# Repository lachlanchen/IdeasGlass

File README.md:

[English](README.md) · [العربية](i18n/README.ar.md) · [Español](i18n/README.es.md) · [Français](i18n/README.fr.md) · [日本語](i18n/README.ja.md) · [한국어](i18n/README.ko.md) · [Tiếng Việt](i18n/README.vi.md) · [中文 (简体)](i18n/README.zh-Hans.md) · [中文（繁體）](i18n/README.zh-Hant.md) · [Deutsch](i18n/README.de.md) · [Русский](i18n/README.ru.md)

# IdeasGlass

*A wearable AI glass that turns ideas into actions, income, and creative momentum.*

> Voice-first wearable AI pipeline: capture from ESP32 glasses, process in FastAPI, and monitor/control via a live PWA dashboard.

| Lane | Purpose |
|---|---|
| 🎙️ Wearable capture | ESP32 glasses send audio, photos, and telemetry in near-real-time |
| 🧠 Backend intelligence | FastAPI ingests streams, transcribes, segments, and persists metadata |
| 🖥️ Dashboard | PWA shows live waveform, transcripts, and device/account status |

<div align="center">

  <br/>
  <sub>App UI (left) · Hardware (right)</sub>
</div>

Explore community experiments at <a href="https://onlyideas.art">onlyideas.art</a>.

## 🚀 Overview

IdeasGlass is an AI-first wearable system for voice-first idea capture and execution. In this repository, the primary runtime path is:

- `backend/glass/` for FastAPI APIs, WebSocket ingest, Whisper-based transcription, and the installable PWA dashboard.
- `IdeaGlass/firmware/ideasglass_arduino/IdeasGlassClient/` for XIAO ESP32S3 firmware streaming telemetry/audio/photos.

If you are new to this repo, start there first.

## 📚 Table of Contents

- [🚀 Overview](#-overview)
- [✨ Why IdeasGlass](#-why-ideasglass)
- [🧩 Features](#-features)
- [🔄 Sample Workflow](#-sample-workflow)
- [🗂️ Project Structure](#-project-structure)
- [🧰 Prerequisites](#-prerequisites)
- [⚙️ Installation](#️-installation)
- [▶️ Usage](#️-usage)
- [🛠️ Configuration](#️-configuration)
- [🧪 Examples](#-examples)
- [🧭 Development Notes](#-development-notes)
- [🆘 Troubleshooting](#️-troubleshooting)
- [🌐 Ecosystem Links](#-ecosystem-links)
- [🙏 Acknowledgements](#-acknowledgements)
- [🛣️ Roadmap](#️-roadmap)
- [🤝 Contribution](#-contribution)
- [❤️ Support](#-support)
- [📄 License](#-license)

### At a glance

| Area | Primary location | What it does |
|---|---|---|
| Backend API + PWA | `backend/glass/` | FastAPI endpoints, WebSocket ingest/fanout, transcription, dashboard |
| Firmware | `IdeaGlass/firmware/ideasglass_arduino/IdeasGlassClient/` | ESP32 capture/streaming client |
| Bridge notes | `references/ideasglass_bridge.md` | TLS/WAN reliability notes and deployment field tips |
| README translations | `i18n/` | Multilingual docs synced from the canonical README |

## ✨ Why IdeasGlass

IdeasGlass is an AI-first wearable built for people who live in streams of ideas. It captures, translates, organizes, and executes on creativity the moment inspiration strikes, whether you are narrating a concept in motion or hosting a live session.

## 🧩 Features

### Product vision features

- **Creation-native hardware** – lightweight glasses and wearable inputs, tuned for voice-first capture plus subtle gesture shortcuts.
- **Instant translation** – real-time language detection/translation so you can ideate across teams or audiences without switching tools.
- **EchoMind co-pilot** – tight pairing with `chat.lazying.art` for brainstorming, script drafting, and multilingual content coaching.
- **Channel autopilot** – drafts outlines, long-form scripts, short-form hooks, and schedules uploads to YouTube or other feeds.
- **Highlights & reels** – auto-selects moments, generates thumbnails, subtitles, and social-ready clips.
- **Income layer** – connects to LazyingArt Coin for tipping, credit payouts, and conversion to on-chain assets.
- **Spending & focus** – tracks operational spend, surfaces profitable formats, and distills your personal strengths into next projects.

### Repository/runtime features

- FastAPI backend with REST + WebSocket endpoints for ingest (`/api/v1/audio`, `/ws/audio-ingest`) and live stream fanout (`/ws/stream`).
- Deterministic audio segmentation (default ~15 s with overlap) into `backend/glass/audio_segments/`.
- Optional openai-whisper streaming transcripts with configurable latency thresholds.
- Optional Postgres persistence (`DATABASE_URL`) for messages, photos, chunks, segments, transcripts.
- PWA dashboard with live waveform, transcript updates, and install support on desktop/mobile.
- Arduino firmware support for XIAO ESP32S3 Sense camera + mic flows.

## 🔄 Sample Workflow

1. **Capture** – Speak or sketch a concept; IdeasGlass transcribes, translates, and tags the intent.
2. **Co-create** – EchoMind refines the idea, drafts scripts, and suggests CTAs tailored for each platform.
3. **Publish** – The channel agent auto-produces highlight videos, gallery images, and uploads them with metadata.
4. **Monetize** – Credits route through LazyingArt Coin (`coin.lazying.art`) and payouts sync with your preferred wallets.
5. **Reflect** – Spending, reach, and engagement dashboards surface what to double down on next.

## 🗂️ Project Structure

```text
IdeasGlass/
├── README.md
├── i18n/                                  # README translations
├── backend/
│   ├── glass/                             # Primary FastAPI + PWA backend
│   │   ├── app.py
│   │   ├── serve.py
│   │   ├── requirements.txt
│   │   ├── static/
│   │   ├── tools/
│   │   └── audio_segments/
│   ├── tornado_app/                       # Secondary/parallel ingest backend path
│   ├── memo/
│   ├── memo_legacy/
│   └── ngrok_bridge/
├── IdeaGlass/firmware/ideasglass_arduino/
│   ├── IdeasGlassClient/
│   ├── config.h
│   ├── WifiTest/WifiTest.ino
│   ├── wifi_credentials.example.h
│   └── README.md
├── references/ideasglass_bridge.md        # Bridge + deployment notes
├── docs/                                  # Additional site/docs assets
├── development_plan/
├── app/
├── ops/observability/
├── ios-app-example/
├── figs/
├── seeed_studio_xiao_esp32s3_dev/
└── .auto-readme-work/
```

## 🧰 Prerequisites

- Python 3.10+
- `pip` (or conda environment with compatible Python)
- Optional: NVIDIA GPU + CUDA/cuDNN for faster Whisper inference
- Optional: PostgreSQL for persistence
- For firmware: Arduino IDE or `arduino-cli`, Seeed XIAO ESP32S3 Sense, PSRAM enabled

| Component | Requirement | Notes |
|---|---|---|
| Backend runtime | Python 3.10+, `pip` | Use venv or conda (`glass`) |
| GPU acceleration (optional) | NVIDIA + CUDA/cuDNN | Improves Whisper latency |
| Persistence (optional) | PostgreSQL | Enabled via `DATABASE_URL` |
| Firmware toolchain | Arduino IDE / `arduino-cli` | Use XIAO ESP32S3 profile with PSRAM |

## ⚙️ Installation

### Backend dependencies

```bash
cd backend/glass
python -m venv .venv
source .venv/bin/activate
pip install -r requirements.txt
```

### Firmware prerequisites

- Copy `IdeaGlass/firmware/ideasglass_arduino/wifi_credentials.example.h` to `wifi_credentials.h` (recommended) and set SSID/password.
- In Arduino IDE, use board `ESP32 -> XIAO_ESP32S3` with `PSRAM: OPI PSRAM`.
- Partition scheme: `Default with spiffs (3MB APP/1.5MB SPIFFS)` or `Maximum APP` when filesystem is not needed.

## ▶️ Usage

### Run backend (uvicorn)

```bash
IDEASGLASS_WHISPER_MODEL=base IDEASGLASS_WHISPER_DEVICE=cuda \
uvicorn backend.glass.app:app \
  --host 0.0.0.0 \
  --port 8765 \
  --proxy-headers \
  --forwarded-allow-ips="*" \
  --reload
```

### Run backend (helper)

```bash
python backend/glass/serve.py --whisper-model base --whisper-device cuda --reload
```

### Open dashboard

- `http://localhost:8765/`
- `http://localhost:8765/healthz`

| Endpoint | Purpose |
|---|---|
| `/` | Main dashboard (PWA-capable UI) |
| `/healthz` | Backend liveness check |
| `/ws/audio-ingest` | Device ingest WebSocket |
| `/ws/stream` | Live stream fanout to dashboard clients |

### Login and bind your device

1. Register or login from the dashboard Settings/Account area.
2. Bind your device ID in the `Bind device` field.
3. Only bound devices will stream to your account.

Generate a device ID + QR image:

```bash
python backend/glass/tools/generate_device_id.py --out logs/device-id.png
```

Bind through API (cookie session required):

```bash
curl -X POST http://localhost:8765/api/v1/devices/bind \
  -H 'Content-Type: application/json' \
  -d '{"device_id":"<your-device-id>"}' \
  -b cookies.txt -c cookies.txt
```

Verify current account and bound devices:

```bash
curl -s http://localhost:8765/api/v1/auth/me -b cookies.txt -c cookies.txt | jq
```

Optional migration (rename historical data to a new device ID):

```bash
curl -X POST http://localhost:8765/api/v1/devices/rename \
  -H 'Content-Type: application/json' \
  -d '{"from_id":"old-id","to_id":"<your-device-id>"}' \
  -b cookies.txt -c cookies.txt
```

### Firmware build/upload (Arduino CLI)

```bash
FQBN='esp32:esp32:XIAO_ESP32S3:PartitionScheme=default_8MB,PSRAM=opi'
SKETCH='IdeaGlass/firmware/ideasglass_arduino/IdeasGlassClient'
PORT='/dev/ttyACM0'

bin/arduino-cli compile --fqbn "$FQBN" "$SKETCH"
bin/arduino-cli upload -p "$PORT" --fqbn "$FQBN" "$SKETCH"
```

If port is busy: `fuser -k /dev/ttyACM0`.
If permission denied: `sudo usermod -aG dialout $USER` then re-login (or temporary `sudo chmod a+rw /dev/ttyACM0`).

### Firmware power UX (XIAO ESP32S3)

- Hold the button ~0.8 s at power-up to boot.
- Hold ~2.5 s while running to enter deep sleep.
- Short press while running still triggers capture.

## 🛠️ Configuration

### Core environment variables

- `DATABASE_URL`: optional Postgres DSN for persistent storage.
- `IDEASGLASS_WHISPER_MODEL`: `base` (default), `small`, `medium`, `large-v3`, `large-v3-turbo`.
- `IDEASGLASS_WHISPER_DEVICE`: `cuda` or `cpu`.
- `IDEASGLASS_WHISPER_FP16`: `1` for GPU mixed precision, `0` for CPU.
- `IDEASGLASS_TRANSCRIBE`: `1` (default) to enable transcription, `0` to disable.
- `IDEASGLASS_TRANSCRIPT_INTERVAL_MS`: rolling transcript interval.
- `IDEASGLASS_TRANSCRIPT_THRESHOLDS_MS`: comma-separated thresholds (default `3000,6000,15000`).

| Variable | Default / options | Effect |
|---|---|---|
| `DATABASE_URL` | unset by default | Enables Postgres persistence for account/device data |
| `IDEASGLASS_WHISPER_MODEL` | `base` (`small`, `medium`, `large-v3`, `large-v3-turbo`) | Controls accuracy vs latency |
| `IDEASGLASS_WHISPER_DEVICE` | `cuda` or `cpu` | Inference backend |
| `IDEASGLASS_WHISPER_FP16` | `1` GPU, `0` CPU-safe | Mixed precision control |
| `IDEASGLASS_TRANSCRIBE` | `1` | Toggle transcription pipeline |
| `IDEASGLASS_TRANSCRIPT_INTERVAL_MS` | runtime configured | Rolling transcript push interval |
| `IDEASGLASS_TRANSCRIPT_THRESHOLDS_MS` | `3000,6000,15000` | Progressive transcript emission thresholds |

Safe `DATABASE_URL` examples:

- `export DATABASE_URL="postgresql://<db_user>@localhost/ideasglass_db"` (peer/local auth)
- `export DATABASE_URL="postgresql://<db_user>:<db_password>@localhost/ideasglass_db"` (password auth)

### Audio gain and segmentation knobs

- `IDEASGLASS_GAIN_TARGET` (default `0.032`)
- `IDEASGLASS_GAIN_MAX` (default `1.8`)
- `IDEASGLASS_GAIN_MIN_RMS` (default `0.008`)
- `IDEASGLASS_SPEECH_RMS` (default `0.03`)
- `IDEASGLASS_SPEECH_MARGIN` (default `0.005`)
- `IDEASGLASS_SEGMENT_TARGET_MS` (default `15000`)
- `IDEASGLASS_SEGMENT_OVERLAP_MS` (default `2000`)
- `IDEASGLASS_SEGMENT_GAIN_TARGET` (defaults to chunk gain target)

| Audio knob | Default | Purpose |
|---|---|---|
| `IDEASGLASS_GAIN_TARGET` | `0.032` | Target RMS normalization |
| `IDEASGLASS_GAIN_MAX` | `1.8` | Upper clamp for gain amplification |
| `IDEASGLASS_GAIN_MIN_RMS` | `0.008` | Floor to avoid amplifying near-silence |
| `IDEASGLASS_SPEECH_RMS` | `0.03` | Speech activity RMS baseline |
| `IDEASGLASS_SPEECH_MARGIN` | `0.005` | Margin around speech threshold |
| `IDEASGLASS_SEGMENT_TARGET_MS` | `15000` | Segment length target |
| `IDEASGLASS_SEGMENT_OVERLAP_MS` | `2000` | Segment overlap for continuity |
| `IDEASGLASS_SEGMENT_GAIN_TARGET` | inherits chunk gain | Segment-level normalization target |

### Model prefetch (optional)

```bash
python backend/glass/tools/prefetch_whisper_models.py \
  --models tiny,base,small,medium,large-v3 \
  --device cuda \
  --fp16 1
```

## 🧪 Examples

### Generate and bind a device ID

```bash
python backend/glass/tools/generate_device_id.py --out logs/device-id.png
```

Then set `kDeviceId` in:

- `IdeaGlass/firmware/ideasglass_arduino/IdeasGlassClient/IdeasGlassClient.ino`

Dashboard flow:

1. Register/login in Settings.
2. Bind the device in the Account panel.
3. Only bound devices stream to your account.

### REST ingest examples

```bash
curl -X POST http://localhost:8765/api/v1/messages \
  -H 'Content-Type: application/json' \
  -d '{"device_id":"dev-001","message":"hello from curl"}'
```

```bash
curl -X POST http://localhost:8765/api/v1/messages \
  -H 'Content-Type: application/json' \
  -d '{
    "device_id":"dev-001",
    "message":"photo demo",
    "photo_base64":"'"$(base64 -w0 sample.jpg)'"',
    "photo_mime":"image/jpeg"
  }'
```

```bash
rec --bits 16 --channels 1 --rate 16000 -c 1 -b 16 -e signed-integer temp.raw trim 0 0.25
curl -X POST http://localhost:8765/api/v1/audio \
  -H 'Content-Type: application/json' \
  -d '{
    "device_id":"dev-001",
    "sample_rate":16000,
    "bits_per_sample":16,
    "duration_ms":250,
    "rms":0.05,
    "audio_base64":"'"$(base64 -w0 temp.raw)'"'
  }'
```

```bash
curl http://localhost:8765/api/v1/audio/segments | jq '.[0]'
curl -o latest.wav http://localhost:8765/api/v1/audio/segments/<segment-id>
```

## 🧭 Development Notes

### Focus area

This repo contains multiple backend tracks. Current contributor guidance and runtime focus is `backend/glass/` unless otherwise requested.

### Static/syntax check

```bash
python -m compileall backend/glass/app.py
```

### Developer docs

- [IdeasGlass Object Analysis](OmiGlass/docs/ideasglass_analysis.mdx)
- [Arduino Hardware Blueprint](OmiGlass/docs/ideasglass_arduino_hardware.md)
- [Multi-platform App / PWA Plan](OmiGlass/docs/ideasglass_pwa_plan.md)
- [Bridge & Arduino HTTPS Client](docs/ideasglass_bridge.md)

> Note: In the current repository snapshot, some historical links above appear to have moved (for example, bridge notes now exist at `references/ideasglass_bridge.md`). The original links are preserved as canonical README content.

### Quick device binding (preserved workflow)

- Generate ID (in conda `glass`): `python backend/glass/tools/generate_device_id.py`
- Set it in firmware: `IdeaGlass/firmware/ideasglass_arduino/IdeasGlassClient/IdeasGlassClient.ino` (`kDeviceId`)
- Run backend and open `http://localhost:8765`, register/login, then bind the device ID in the Account panel

## 🆘 Troubleshooting

- **Port already in use:** run backend on another port and update client settings.
- **Serial port busy:** `fuser -k /dev/ttyACM0`.
- **Linux serial permission denied:** `sudo usermod -aG dialout $USER` and re-login.
- **Postgres unavailable:** backend can run without DB for partial functionality; verify `DATABASE_URL` and restart.
- **Whisper performance issues:** use smaller models (`base`/`small`) or disable transcription via `IDEASGLASS_TRANSCRIBE=0`.
- **TLS/time sync instability on ESP32:** verify Wi-Fi, NTP availability (UDP/123), and cert/host settings; see `references/ideasglass_bridge.md` for detailed field notes.
- **No live waveform updates:** check backend logs and browser console for `[IdeasGlass][wave]` traces and confirm `/ws/stream` connectivity.

## 🌐 Ecosystem Links

| Brand | Purpose | Link |
|---|---|---|
| 🧠 EchoMind | Multilingual AI companion for learning and creation | [chat.lazying.art](https://chat.lazying.art) |
| 🌱 OnlyIdeas | Research-to-product community for bold concepts | [onlyideas.art](https://onlyideas.art) |
| 💸 LazyEarn | Automations to turn small wins into income | [earn.lazying.art](https://earn.lazying.art) |
| 📚 LazyLearn | Physics & chemistry tracks and notebooks | [learn.lazying.art](https://learn.lazying.art) |
| 🤖 IdeasRobot | Agent that turns ideas into drafts, tasks, and posts | [robot.lazying.art](https://robot.lazying.art) |
| 👓 IdeasGlass | Capture, translate, and auto-produce highlight reels | [glass.lazying.art](https://glass.lazying.art) |
| 🪙 LazyingArt Coin | Rewards and payouts bridging contributions and on-chain value | [coin.lazying.art](https://coin.lazying.art) |
| 🧪 IDEAS | Notebook of research notes and essays | [ideas.onlyideas.art](https://ideas.onlyideas.art) |
| 🎨 LazyingArt | Studio behind OnlyIdeas, EchoMind, LazyEdit, and IdeasGlass | [lazying.art](https://lazying.art) |

## 🙏 Acknowledgements

We stand on the shoulders of great open projects — thank you to:

- <a href="https://www.omi.me/?ref=LazyingArt" target="_blank" rel="noopener" style="display:inline-flex;align-items:center;justify-content:center;padding:0.45rem 1rem;border-radius:999px;background:#111827;color:#ffffff;font-weight:700;text-decoration:none;">Get OmiGlass (BasedHardware)</a>
  - **Referral Program** — Use coupon `LazyingArt` to save 10% (30% commission unlocks after 10 sales).

    <div style="display:flex;flex-wrap:wrap;gap:0.4rem;margin:0.3rem 0;">
      <a href="https://www.omi.me/?ref=LazyingArt" target="_blank" rel="noopener" style="display:inline-flex;align-items:center;justify-content:center;padding:0.45rem 1.1rem;border-radius:999px;background:#111827;color:#ffffff;font-weight:700;text-decoration:none;">Get OmiGlass with LazyingArt</a>
      <a href="https://discord.com/invite/8MP3b9ymvx?ref=LazyingArt" target="_blank" rel="noopener" style="display:inline-flex;align-items:center;justify-content:center;padding:0.45rem 1rem;border-radius:999px;background:#2563eb;color:#ffffff;font-weight:700;text-decoration:none;">Join Omi Discord</a>
      <a href="https://www.seeedstudio.com/Seeed-XIAO-BLE-Sense-nRF52840-p-5253.html" target="_blank" rel="noopener" style="display:inline-flex;align-items:center;justify-content:center;padding:0.45rem 1rem;border-radius:999px;background:#059669;color:#ffffff;font-weight:700;text-decoration:none;">Buy Seeed XIAO BLE Sense</a>
    </div>
- OpenAI Whisper: https://github.com/openai/whisper
- WhisperX: https://github.com/m-bain/whisperX
- Ollama: https://github.com/ollama/ollama

## 🛣️ Roadmap

- Harden and document the end-to-end audio streaming path across WAN/TLS environments.
- Continue improving transcript quality/latency tradeoffs (model/device/threshold presets).
- Expand device management and account-scoped multi-device workflows in the dashboard.
- Align or consolidate legacy/parallel backend tracks (`tornado_app`, `memo`, `memo_legacy`, `ngrok_bridge`) with the primary `backend/glass` path.
- Maintain and refresh multilingual README variants under `i18n/`.

## 🤝 Contribution

Contributions are welcome. For repository-specific workflow guidance, follow `AGENTS.md`.

Recommended local validation before opening a PR:

```bash
python -m compileall backend/glass/app.py
```

When submitting changes:

- Keep commit subjects short and action-driven (present tense).
- Mention relevant env vars (for example `IDEASGLASS_TRANSCRIPT_THRESHOLDS_MS`) in PR notes when behavior depends on them.
- Include testing evidence (backend logs, dashboard behavior, firmware output).
- Never commit secrets (`DATABASE_URL`, API tokens, credentials files).

## ❤️ Support

<!-- support:start -->

<!-- support:end -->

## 📄 License

No top-level `LICENSE` file was detected in this repository snapshot. Until an explicit license file is added, treat usage and redistribution as requiring maintainer approval.

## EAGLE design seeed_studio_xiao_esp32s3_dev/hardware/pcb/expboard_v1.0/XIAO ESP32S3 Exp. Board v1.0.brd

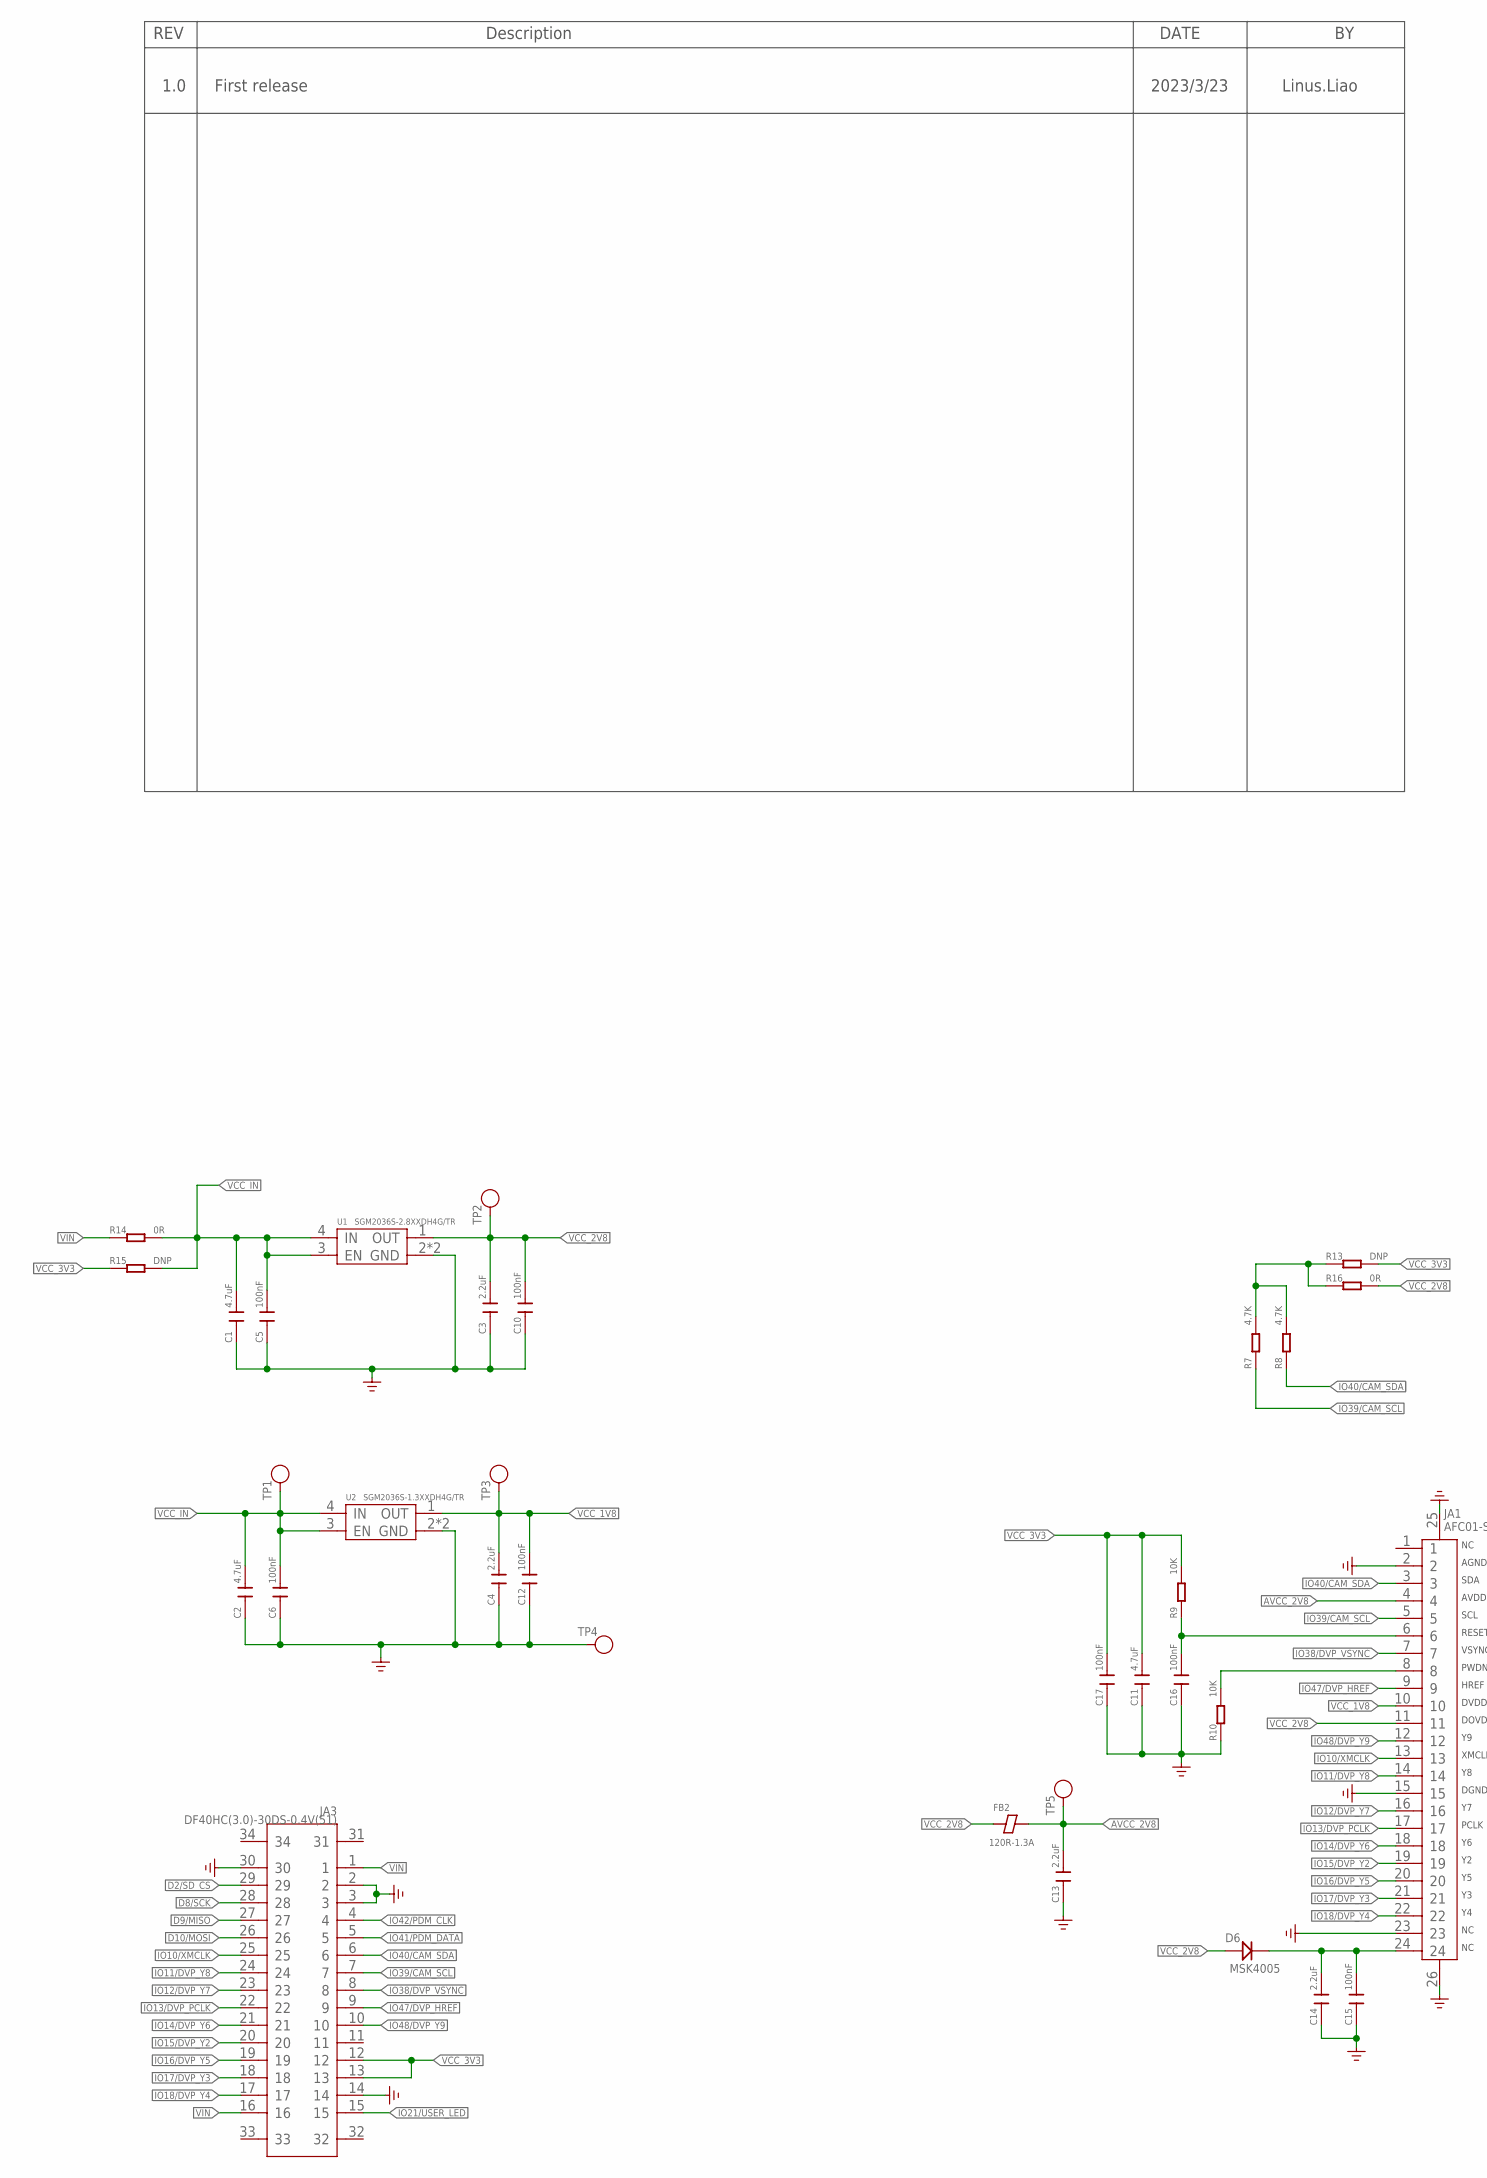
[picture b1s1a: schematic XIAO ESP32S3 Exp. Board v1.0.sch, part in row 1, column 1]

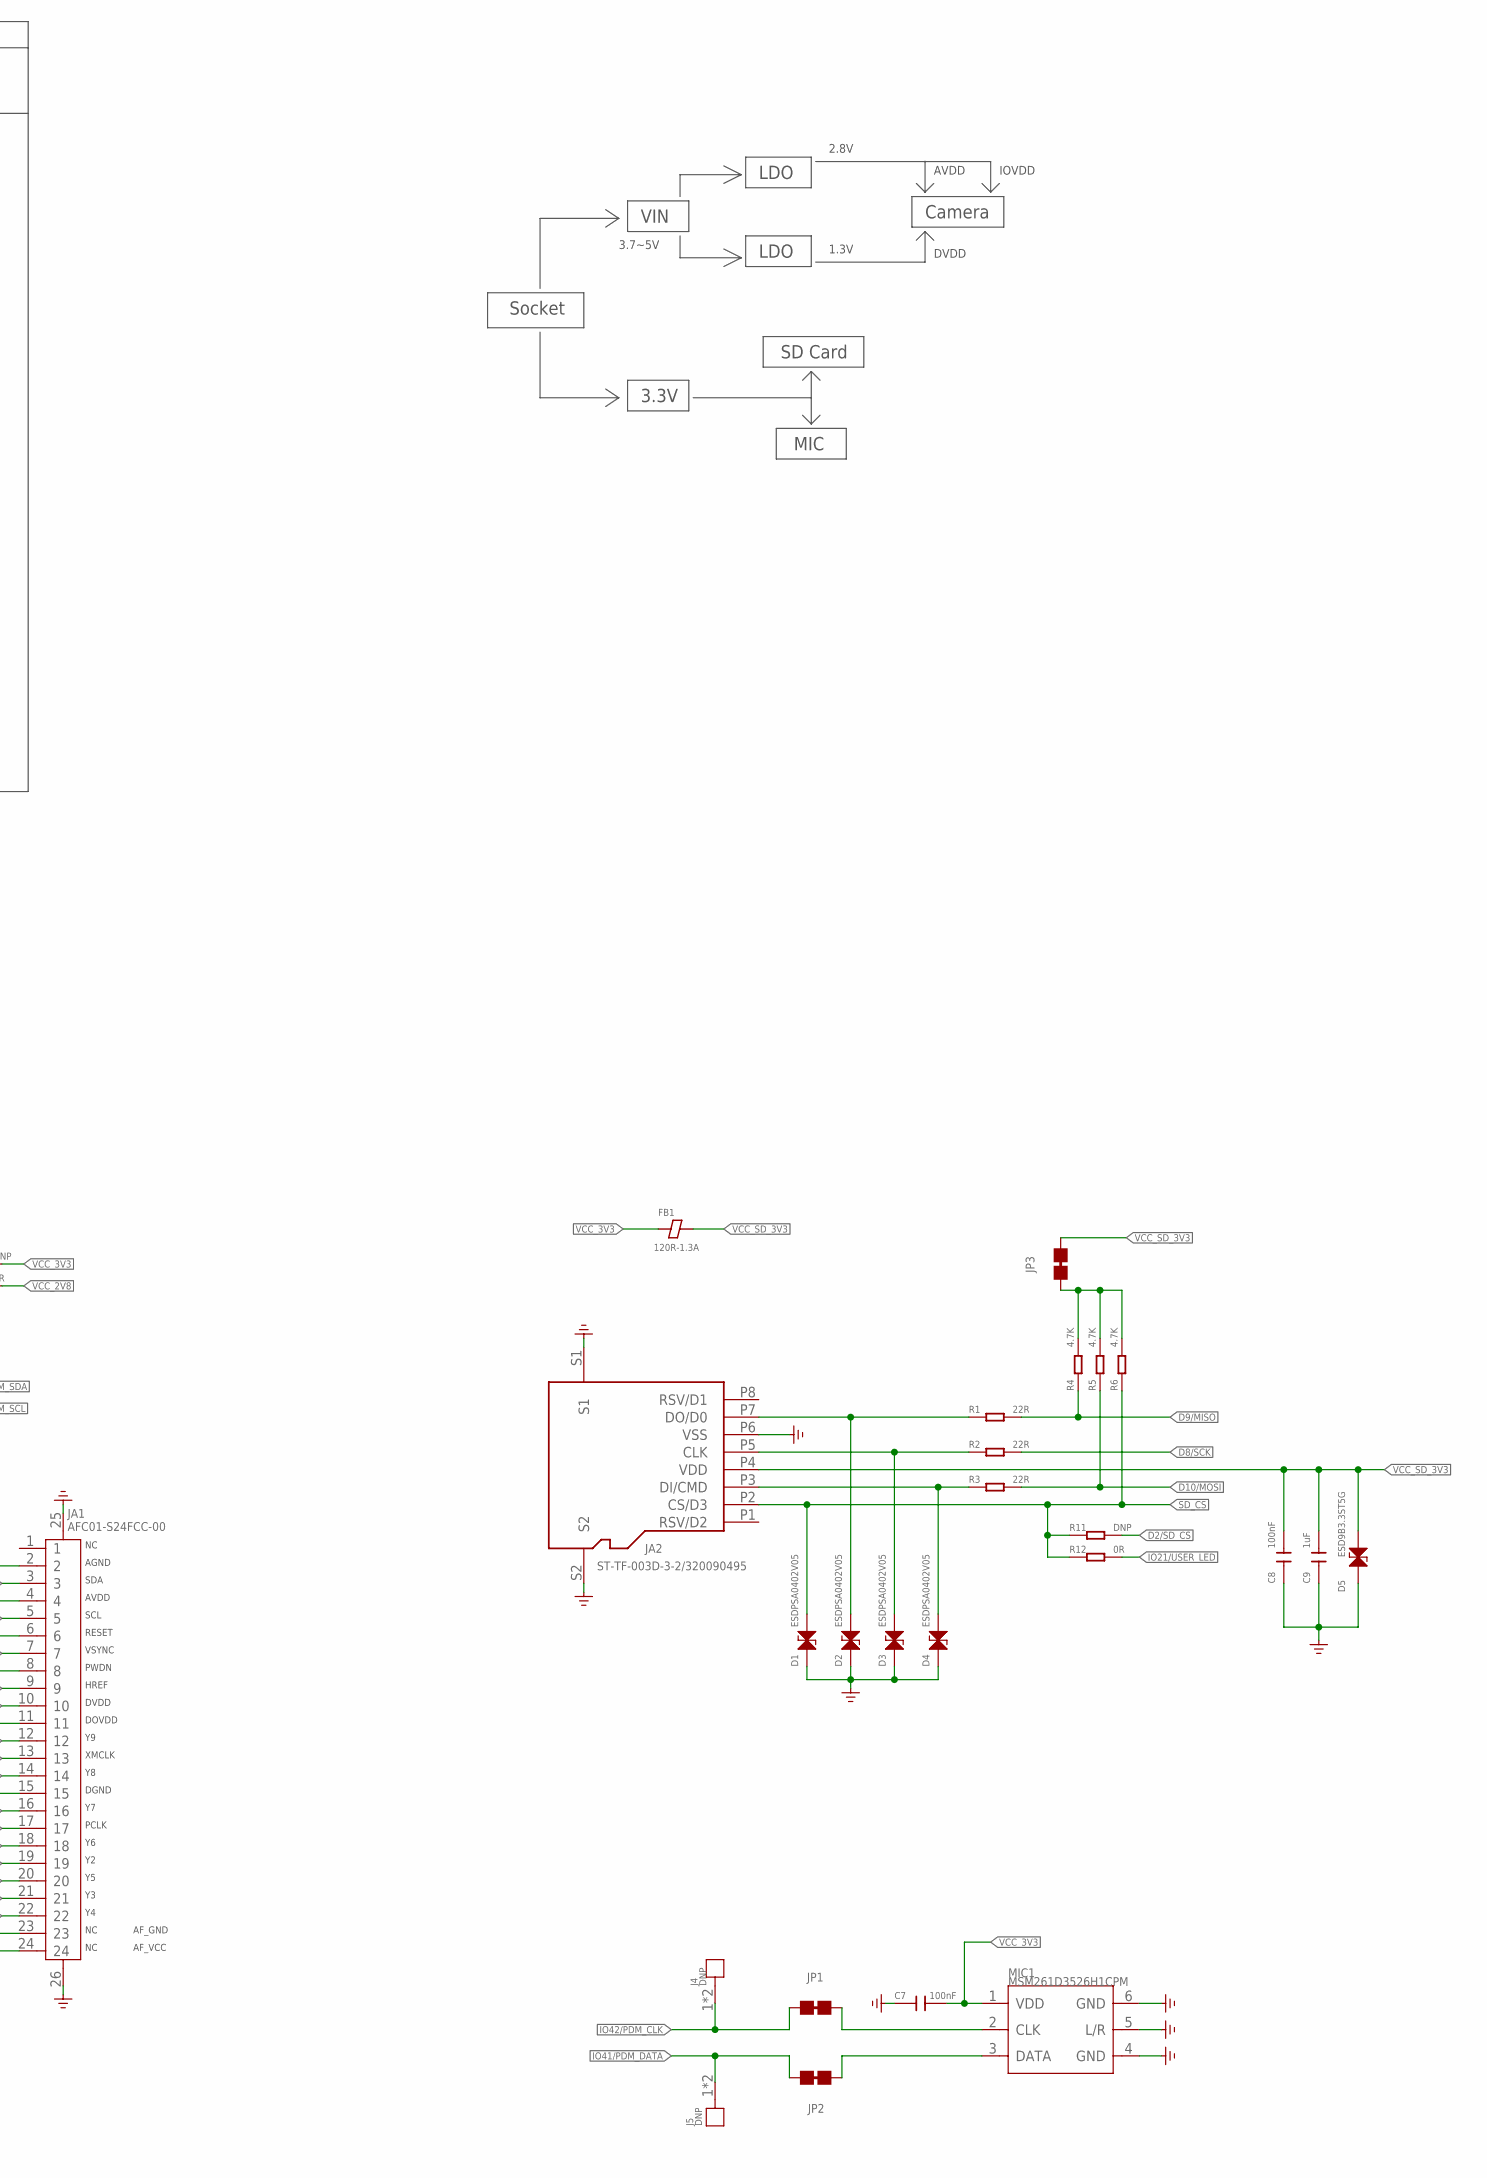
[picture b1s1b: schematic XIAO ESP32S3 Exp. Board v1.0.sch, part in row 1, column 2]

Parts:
C1, C2, C11: 4.7uF; C0402
C3, C4, C13, C14: 2.2uF; C0402
C5, C6, C7, C8, C10, C12, C15, C16, C17: 100nF; C0402
C9: 1uF; C0402
D1, D2, D3, D4: ESDPSA0402V05; ESD-0402-NO-SILK
D5: ESD9B3.3ST5G; ESD-0402-NO-SILK
D6: MSK4005; SOD-523
FB1, FB2: 120R-1.3A; F0402
J4, J5: DNP; H1-HALF-HOLE-2.54
JA1: AFC01-S24FCC-00; FPCB24-SMD-0.5-17.6X5.0X2MM
JA2: ST-TF-003D-3-2/320090495; MICRO-SD8+2P-SMD-1.1-11.41X4.9X3MM
JA3: DF40HC(3.0)-30DS-0.4V(51); BTB30-0.4-8.6X3.38X2.4MM
JP1, JP2, JP3: JP-2P-SHORT; 2P-SMD-0603
MIC1: MSM261D3526H1CPM; MIC6P-3.5X2.65X0.94MM
R1, R2, R3: 22R; R0402
R4, R5, R6, R7, R8: 4.7K; R0402
R9, R10: 10K; R0402
R11, R13, R15: DNP; R0402
R12, R14, R16: 0R; R0402
TP1, TP2, TP3, TP4, TP5: TEST-POINT-35; TP_3535
U1: SGM2036S-2.8XXDH4G/TR; X2SON-4
U2: SGM2036S-1.3XXDH4G/TR; X2SON-4

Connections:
AVCC_2V8: C13.2, FB2.2, JA1.4, TP5.T
D2/SD_CS: JA3.29, R11.2
D8/SCK: JA3.28, R2.2
D9/MISO: JA3.27, R1.2, R4.1
D10/MOSI: JA3.26, R3.2, R5.1
GND: C1.1, C2.1, C3.1, C4.1, C5.1, C6.1, C7.1, C8.1, C9.1, C10.1, C11.1, C12.1, C13.1, C14.1, C15.1, C16.1, C17.1, D1.1, D2.1, D3.1, D4.1, D5.1, JA1.2, JA1.15, JA1.23, JA1.25 (P1), JA1.26 (P2), JA2.P6 (VSS), JA2.S1, JA2.S2, JA3.2, JA3.3, JA3.14, JA3.30, MIC1.4 (GND), MIC1.5 (L/R), MIC1.6 (GND), R10.1, TP4.T, U1.2 (GND), U1.T (GND), U2.2 (GND), U2.T (GND)
IO10/XMCLK: JA1.13, JA3.25
IO11/DVP_Y8: JA1.14, JA3.24
IO12/DVP_Y7: JA1.16, JA3.23
IO13/DVP_PCLK: JA1.17, JA3.22
IO14/DVP_Y6: JA1.18, JA3.21
IO15/DVP_Y2: JA1.19, JA3.20
IO16/DVP_Y5: JA1.20, JA3.19
IO17/DVP_Y3: JA1.21, JA3.18
IO18/DVP_Y4: JA1.22, JA3.17
IO21/USER_LED: JA3.15, R12.2
IO38/DVP_VSYNC: JA1.7, JA3.8
IO39/CAM_SCL: JA1.5, JA3.7, R7.1
IO40/CAM_SDA: JA1.3, JA3.6, R8.1
IO41/PDM_DATA: J5.1, J5.2, JA3.5, JP2.P2 (2)
IO42/PDM_CLK: J4.1, J4.2, JA3.4, JP1.P1 (1)
IO47/DVP_HREF: JA1.9, JA3.9
IO48/DVP_Y9: JA1.12, JA3.10
unnamed: JP1.P2 (2), MIC1.2 (CLK)
unnamed: JP2.P1 (1), MIC1.3 (DATA)
unnamed: D2.2, JA2.P7 (DO/D0), R1.1
unnamed: D3.2, JA2.P5 (CLK), R2.1
unnamed: JP3.P1 (1), R4.2, R5.2, R6.2
unnamed: D4.2, JA2.P3 (DI/CMD), R3.1
unnamed: C16.2, JA1.6, R9.1
unnamed: C14.2, C15.2, D6.-, JA1.24
unnamed: R7.2, R8.2, R13.1, R16.1
unnamed: JA1.8, R10.2
SD_CS: D1.2, JA2.P2 (CS/D3), R6.1, R11.1, R12.1
VCC_1V8: C4.2, C12.2, JA1.10, TP3.T, U2.1 (OUT)
VCC_2V8: C3.2, C10.2, D6.+, FB2.1, JA1.11, R16.2, TP2.T, U1.1 (OUT)
VCC_3V3: C7.2, C11.2, C17.2, FB1.1, JA3.12, JA3.13, MIC1.1 (VDD), R9.2, R13.2, R15.1
VCC_IN: C1.2, C2.2, C5.2, C6.2, R14.2, R15.2, TP1.T, U1.3 (EN), U1.4 (IN), U2.3 (EN), U2.4 (IN)
VCC_SD_3V3: C8.2, C9.2, D5.2, FB1.2, JA2.P4 (VDD), JP3.P2 (2)
VIN: JA3.1, JA3.16, R14.1

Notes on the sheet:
1.0
First release
AGND
SDA
AVDD
SCL
RESET
VSYNC
PWDN
HREF
DVDD
DOVDD
XMCLK
DGND
PCLK
Socket
VIN
LDO
3.3V
Camera
SD Card
MIC
2.8V
1.3V
IOVDD
3.7~5V
AF_GND
AF_VCC
2023/3/23
Linus.Liao

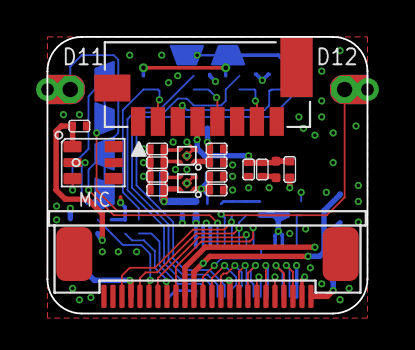
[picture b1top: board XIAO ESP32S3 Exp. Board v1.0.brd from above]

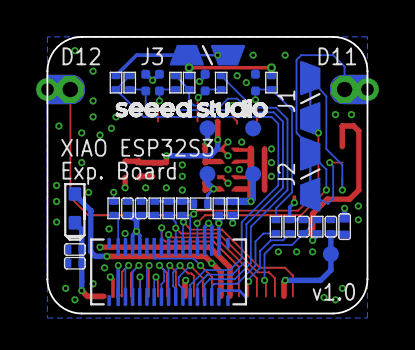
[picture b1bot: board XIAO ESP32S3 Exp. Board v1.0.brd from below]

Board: 4 copper layers, 17.8 x 15.4 mm, 58 parts (38 on the bottom side), 40 nets.

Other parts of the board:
U$6: LOGO-SEEED-NEW-0.94X8.4MM

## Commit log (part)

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2025-11-08 docs: add initial IdeasGlass readme
2025-11-08 docs: streamline donation section
2025-11-08 Add replicated IdeasGlass assets and Seeed XIAO dev kit
2025-11-08 Fix WifiTest include path and doc instructions
2025-11-08 Ignore private workspace directory
2025-11-08 Improve WifiTest logging and network scan
2025-11-08 Add Ngrok bridge backend and Arduino HTTPS client
2025-11-08 Refresh PWA UI with light theme
2025-11-08 Handle JSONB meta when streaming history
2025-11-08 Remove unused esp_spiram include
2025-11-08 Preserve message ordering for history vs realtime
2025-11-08 Flip camera output in firmware and drop backend rotation
2025-11-08 Fix I2S pin initializer order
2025-11-08 fix: use ESP_I2S PDM capture and lengthen segments
2025-11-08 tune audio gain and speech detection
2025-11-08 shorten audio segments to 15s with overlap
2025-11-08 Add WhisperX transcription feed
2025-11-08 Stream live whisper transcripts
2025-11-08 Preload cuDNN for WhisperX
2025-11-08 Tighten whisper streaming thresholds
2025-11-08 Skip streaming transcription during silence
2025-11-08 Emit silence markers at transcript thresholds
2025-11-08 Use shared photo interval constant
2025-11-08 Log photo uploads on serial
2025-11-08 Sort in-memory messages by timestamp
2025-11-08 Optimize photo capture cadence and fix transcript/photo persistence
2025-11-08 Send photos without blocking capture
2025-11-09 Stream photos over dedicated WebSocket
2025-11-09 Add serial logger (defaults to /dev/ttyACM0)
2025-11-09 Docs: Arduino CLI + serial logging + DB correlation workflow
2025-11-09 Observability: add Grafana+Loki+Promtail stack and docs
2025-11-09 Photos: offload base64 decode and always persist in background to keep handlers responsive
2025-11-09 Fix photo_base64 decode: preserve validate=True when offloading to thread
2025-11-09 Docs: add live status verification guide (backend, serial, DB)
2025-11-09 UI: move transcripts below recordings; remove duplicate 'Recent recordings'; keep 'More' button below list
2025-11-09 Tools: add prefetch_whisper_models.py to download/load-test medium, large-v3, etc.
2025-11-09 Firmware: start chunk counter at 1; add WS connect logging, 1s heartbeat ping for photo WS, and HTTP fallback on failure
2025-11-09 Frontend: compress VU mapping and scale so bars are very short and weakly influenced by volume, per request
2025-11-09 Frontend: reduce VU saturation (noise floor=0.015, gain=11) and limit visual scale so bars don’t hit 100% under normal speech
2025-11-09 Frontend: increase VU sensitivity and visual range (gamma 0.8; baseline 25% + level*0.5) so values around 0.5 show larger height changes
2025-11-09 Frontend: add per-bar variance animator (seeded wobble) so VU shows equalizer-like movement while preserving speech vs silence levels
2025-11-09 Tools: fix whisper prefetch encode test by adding batch dimension and matching model device/dtype; fallback to encode()/transcribe on error
2025-11-09 Docs: scrub tunnel references; update paths and names to new backend/bridge and IdeasGlassClient.
2025-11-09 Deps: add email-validator (required by Pydantic EmailStr for register/login)
2025-11-09 Docs: add Device ID & Binding guide (generate ID, flash in firmware, bind via UI/API, verify via /auth/me); fix local URLs and Arduino paths
2025-11-09 Frontend: refine bottom nav (larger icons, translucent background, safe-area padding, softer active pill) and increase body bottom padding to avoid overlap
2025-11-09 UI: halve waveform height; refine Settings layout and device list; compact bottom nav spacing while keeping icons larger and unclipped
2025-11-09 Live: replace photo overlay with proper sub-page (push-style) inside Live; keep lazy-loading; compact grid with More » tile on Live
2025-11-09 UI spacing: further reduce gaps and padding between panels and within Live; tighten gallery grid spacing
2025-11-09 Fix: declare liveTranscripts* before use to avoid TDZ error; move constants to top
2025-11-09 Transcripts: microrefresh compact list to latest 5 on new final; subtle flash highlight; avoid unnecessary re-rendering.
2025-11-09 Chore: include index.html updates for Live push-pages and layout wiring.
2025-11-09 Transcripts page: add time + Play at right for each item; make list items flex with left text and right actions.
2025-11-09 Docs: add missing dashboard screenshots (ideas.lazying.art_main/full).
2025-11-09 Ignore local symlinks (whisperX, OmiGlassReference) and bridge audio output; remove symlinks from repo index.
2025-11-09 Docs: place Ecosystem and Support (Donate) side-by-side in a single row using an HTML table.
2025-11-09 Transcripts: include language code from Whisper; persist in DB; show language badge in live transcript panel and transcript detail page.
2025-11-09 Transcripts UI: show language code in compact and full transcript lists; plumb language through transcript feed and older loads.
2025-11-09 Settings/Status: place Backend status pill inline with Status title; tidy row styles to exclude header; keep WebSocket row as chip.
2025-11-09 Status UI: move Backend status to its own row under the Status title; keep header separate.
2025-11-09 Docs: convert HEIC hardware photo to PNG and add side-by-side composite with app UI (left app, right hardware).
2025-11-09 Docs: show app UI and hardware images side-by-side at full width (each half width).
2025-11-09 Docs: add Acknowledgements — OmiGlass, Whisper, WhisperX, and Ollama.
2025-11-09 Gallery: microrefresh compact gallery on new photo arrival (keeps latest tiles up to date).
2025-11-09 Firmware: add long-press power UX; archive prior Arduino sketch files under firmware/ideasglass_arduino/archived; config knobs for boot/sleep holds.
2025-11-09 Docs: document Start/Stop button UX with LED cues; enumerate button/LED and key pin map (camera, mic, I2C, battery) with tips for spare IO and RTC-wake.
2025-11-09 Firmware: fix TLS time sync + robust Wi‑Fi join; gate WS pings when offline; photo meta types as strings; keep autostart (no long‑press) for upload/charge starts
2025-11-09 Docs: record live behavior — photos smooth (HTTP fallback), audio occasional lag on WSS; add mitigation checklist and verification cues
2025-11-09 Docs: add firmware hardening plan (non-breaking) and link from bridge guide
2025-11-10 Firmware hardening (Stage A, flags off by default): add HTTP keep-alive pooling, battery ADC smoothing, lightweight counters; no behavior change unless flags enabled
2025-11-10 Firmware hardening (Stage C, flags off by default): add non-blocking WS reconnect with exponential backoff+jitter; sender never stalls; default off
2025-11-10 UI: make timer responsive — split 'Recording' and time values; wrap values to next line on small screens
2025-11-10 docs(donate): align footer with profile (centered 2-col table)
2025-11-10 UI: add 'Goal' tab to bottom nav with bullseye icon; wire up goal view and tab state persistence
2025-11-10 UI: keep 'Goal' centered by ordering tabs Live · Ideas · Goal · Creation · Settings
2025-11-10 Goals: add ig_goals DDL + /api/v1/goals (list) + /goals/seed; PWA Goal tab with elegant cards and progress bar
2025-11-10 Fix: remove stray await in setActiveTab causing SyntaxError; make populateIdeaSelect non-blocking
2025-11-10 Goals: make cards clickable to detail subpage with edit/delete; backend GET/PATCH/DELETE goal endpoints; UI form for contents
2025-11-10 Tabs: hide any open sub-pages (idea/goal/creation details, live subpages) on tab change; close modals and pause audio to prevent leaks
2025-11-10 Header: compact spacing and fixed only on Live tab; add body.header-fixed toggle in setActiveTab; reduce height/padding/gap
2025-11-10 Live header: prevent overlap and respect iPhone Dynamic Island — add viewport-fit=cover, default header-fixed class, move safe-area to header padding, body top padding only header height
2025-11-10 Subpages: hide global header on detail/More pages (adds body.hide-header toggle); ensure restored on back/tab change; respect safe-areas
2025-11-10 Header offset: measure runtime header height and set --header-offset; body top padding uses runtime offset to fully clear header across tabs and devices
2025-11-10 Prophecy Diary: add 'diary' narrative field (DDL+API+seed); center detail header title; add Prophecy section; teaser shows diary snippet; display title sans prefix
2025-11-10 Prophecy Diary vision: show richer diary-style paragraph; pre-wrap + comfortable line-height; seed with longer narrative vision
2025-11-10 Creation detail: center the main creation title (scoped to #creationDetailView)
2025-11-10 UI: add language selector (English/繁體中文/简体中文/日本語) with auto-detect, persistence, and i18n for header/nav/major labels
2025-11-10 UX: keep header fixed and scroll to top for Photos/Transcripts ‘More’ pages; stop hiding header on these subpages
2025-11-10 UI: reduce Ideas tab icon to 20x20 (only for Ideas)
2025-11-10 Settings: add Bluetooth (beta) panel with Web Bluetooth scanning on Android (Chrome/Edge), list + Bind via Device Information service when available
2025-11-10 Firmware: make long-press shutdown responsive regardless of Wi‑Fi state; preserve boot hold-to-start via config
2025-11-10 Chore: sync generated __pycache__ changes
2025-11-10 WS: accept and echo client subprotocol for /ws/audio-ingest and /ws/photo-ingest (improves compatibility with custom clients)
2025-11-10 Docs: add release note + postmortem for audio WS rollback
2025-11-10 Firmware: enable Stage A/B/C tuning flags and run Wi-Fi without modem sleep for better streaming
2025-11-10 UI: keep transcript detail header fixed at top when opened
2025-11-13 Docs: add Omi referral + quick links to README
2025-11-13 Docs: render Omi quick links as buttons
2025-11-13 Docs: use CTA button for OmiGlass + update coupon copy
2025-11-23 Docs: add GitHub Pages landing for glass.lazying.art
2025-11-23 Docs: refresh landing page with light, airy theme
2025-11-23 site: add LazyingArt ecosystem links section to IdeasGlass docs landing
2025-11-23 i18n: add language selector + English fallback; wire IdeasGlass docs to use glass.lazying.art
2025-11-23 i18n: add Simplified Chinese hero translations and MetaMask label; fix zh mapping
2025-11-23 i18n: translate IdeasGlass ecosystem section
2025-11-23 Chore: rename backend/bridge to backend/glass
2025-11-23 Docs: rename memo alias to AI Memo
2025-11-23 UI: switch Goal tab to AI Memo chat with local feed
2025-11-23 UI: make AI Memo Goal tab a full-screen chat
2025-11-23 UI: anchor AI Memo chat input above footer nav
2025-11-23 UI: fully pin AI Memo chat input above footer
2025-11-23 UI: add respond toggle and chat attach buttons, chat bubbles styled
2025-11-23 UI: hide legacy goals in Settings and remove install footer
2025-11-23 UI: per-tab header titles, hide duplicate page headings, lighten chat bar
2025-11-30 Chore: checkpoint before glass/memo reshuffle
2025-11-30 Memo nav: move Chat next to Live
2025-11-30 Memo nav: use journal-style icon for Memo tab
2025-11-30 Memo chat: default Respond toggle on
2025-11-30 Memo: generate candidate memos from chat and show confirm list
2025-11-30 Memo: add AI-backed memo suggest endpoint with OpenAI primary, DeepSeek fallback
2025-11-30 Memo: restore selected tab and reload memo candidates after refresh
2025-11-30 Memo: rely on DB-backed candidates and suggestions
2025-11-30 Memo: persist chat to DB, add AI reply injection
2025-11-30 Memo: add editable memo detail with complete/delete and chat layout tweaks
2025-11-30 Memo chat: only send new user messages to AI and show status toasts/system lines
2025-12-28 Add banner to README
2025-12-28 Update project files
2025-12-29 Update README banner
2025-12-29 Add header logo
2025-12-29 Sync ecosystem order
2026-02-28 Draft complete canonical README restructure
